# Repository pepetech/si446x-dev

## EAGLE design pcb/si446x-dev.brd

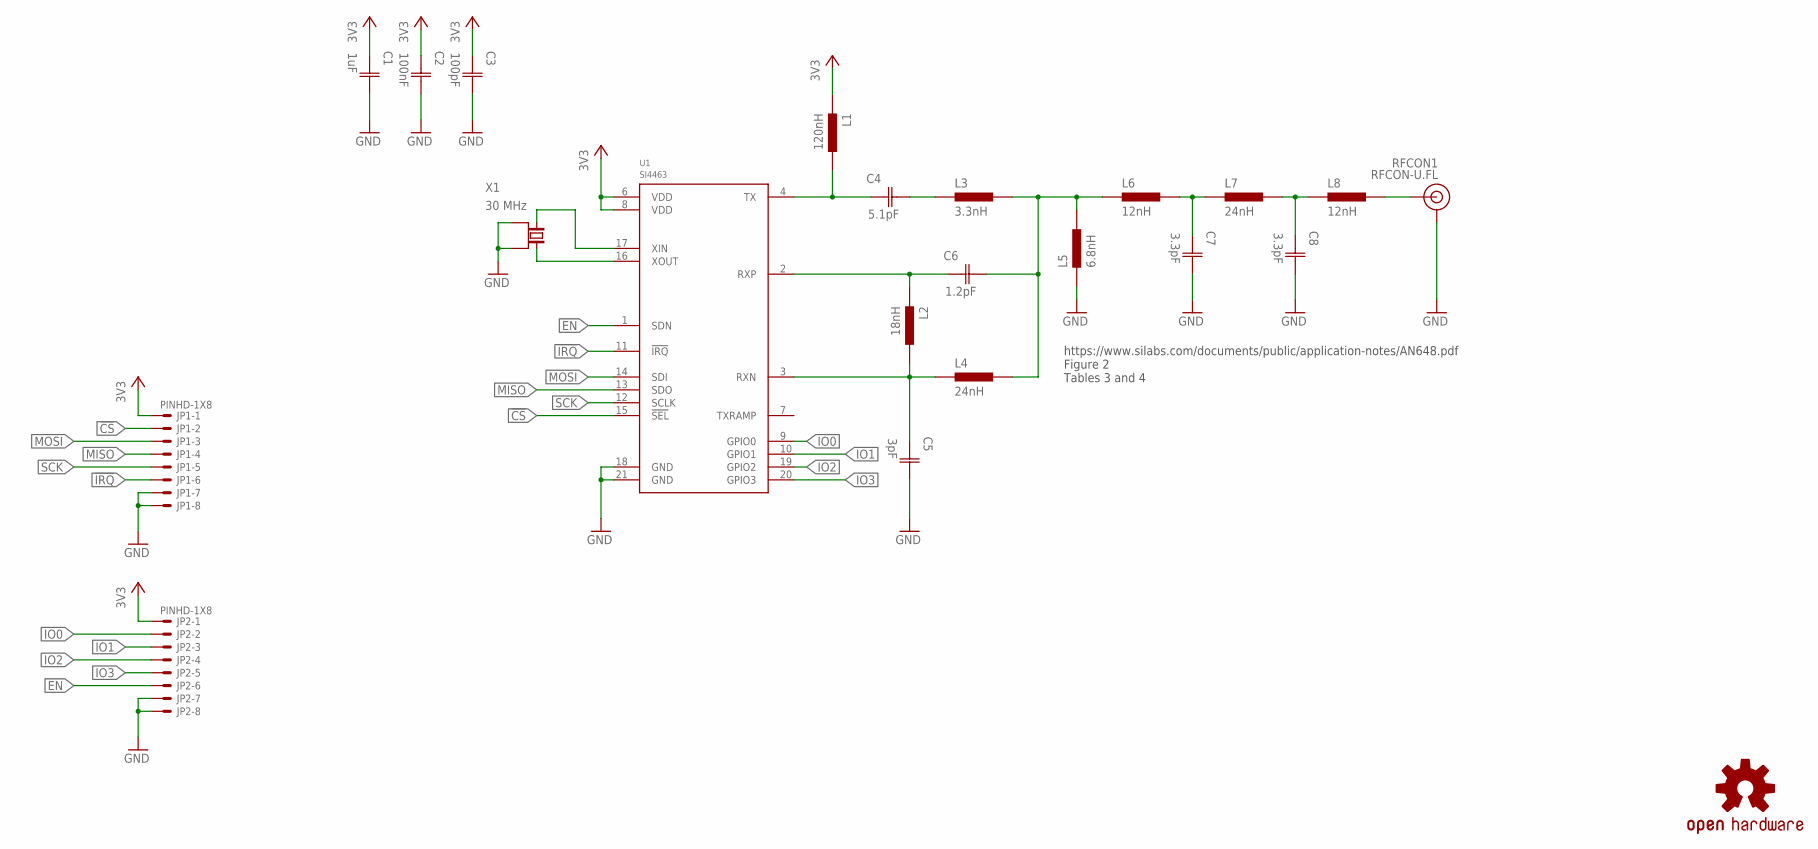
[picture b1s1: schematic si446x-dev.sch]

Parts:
C1: 1uF; CAP0603
C2: 100nF; CAP0603
C3: 100pF; CAP0603
C4: 5.1pF; CAP0603
C5: 3pF; CAP0603
C6: 1.2pF; CAP0603
C7, C8: 3.3pF; CAP0603
JP1, JP2: PINHD-1X8; 1X08
L1: 120nH; IND0603
L2: 18nH; IND0603
L3: 3.3nH; IND0603
L4, L7: 24nH; IND0603
L5: 6.8nH; IND0603
L6, L8: 12nH; IND0603
LOGO1: OSHW-LOGOM; OSHW-LOGO-M
RFCON1: RFCON-U.FL; U.FL
U1: SI4463; QFN20
X1: 30 MHz; 4-SMD-3225

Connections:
3V3: C1.1 (C1), C2.1 (C1), C3.1 (C1), JP1.1, JP2.1, L1.1, U1.6 (VDD), U1.8 (VDD)
!CS: JP1.2, U1.15 (!SEL)
!IRQ: JP1.6, U1.11 (!IRQ)
EN: JP2.6, U1.1 (SDN)
GND: C1.2 (C2), C2.2 (C2), C3.2 (C2), C5.2 (C2), C7.2 (C2), C8.2 (C2), JP1.7, JP1.8, JP2.7, JP2.8, L5.1, RFCON1.P$1 (GND), RFCON1.P$2 (GND), U1.18 (GND), U1.21 (GND), X1.2 (GND), X1.4 (GND)
IO0: JP2.2, U1.9 (GPIO0)
IO1: JP2.3, U1.10 (GPIO1)
IO2: JP2.4, U1.19 (GPIO2)
IO3: JP2.5, U1.20 (GPIO3)
MISO: JP1.4, U1.13 (SDO)
MOSI: JP1.3, U1.14 (SDI)
unnamed: C5.1 (C1), L2.2, L4.1, U1.3 (RXN)
unnamed: C6.1 (C1), L2.1, U1.2 (RXP)
unnamed: C6.2 (C2), L3.2, L4.2, L5.2, L6.1
unnamed: L8.2, RFCON1.P$3 (SIGNAL)
unnamed: C4.2 (C2), L3.1
unnamed: C4.1 (C1), L1.2, U1.4 (TX)
unnamed: C7.1 (C1), L6.2, L7.1
unnamed: C8.1 (C1), L7.2, L8.1
unnamed: U1.16 (XOUT), X1.3 (2)
unnamed: U1.17 (XIN), X1.1
SCK: JP1.5, U1.12 (SCLK)

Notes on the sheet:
https://www.silabs.com/documents/public/application-notes/AN648.pdf Figure 2 Tables 3 and 4

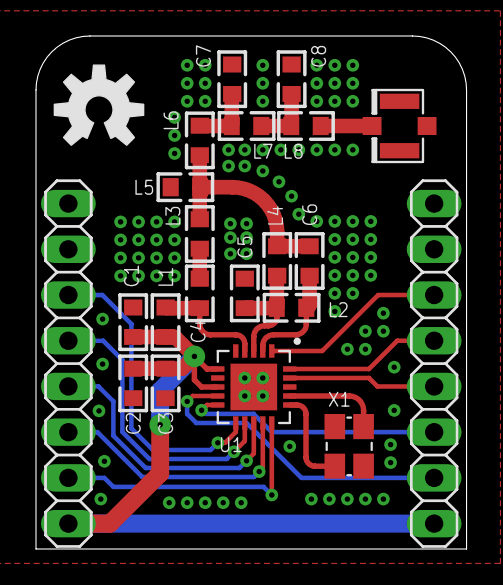
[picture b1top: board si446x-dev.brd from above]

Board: 2 copper layers, 23.9 x 28.5 mm, 22 parts (0 on the bottom side), 22 nets.

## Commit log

2019-05-23 Finish board
2019-05-23 Check DRC and add gerbers
2019-05-26 Update libs
